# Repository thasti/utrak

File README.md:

# uTrak miniature tracker repository

## Abstract 
This repository contains software and hardware design files for uTrak - the tracker of a series of small high altitude balloons. The software is implemented for a MSP430 MCU, with test programs runnable on a PC.
project documentation can be found here: http://www.dooce.de/dokuwiki/doku.php?id=projekte:utrak:start

The following tasks shall be performed by the software:
* Filtering and reading GPGGA-sentences from GPS - extracting position, altitude
* Measuring supply voltage with internal ADC
* Reading die temperature with internal ADC
* Generating telemetry frames (Including position, altitude, supply voltage, temperature)
* Configuring the Si4060 transmitter IC
* Power management for MCU and external hardware
* Transmission of APRS position reports

## GPS input
The MSP430 USART is used to store one NMEA-sentence to RAM (from $ to newline). Filtering and processing is controlled by a simple finite state machine. Fix data (position and altitude) are extracted and converted to HAB telemetry compatible format and APRS frames.

## Telemetry generation
From valid GPS data and telemetry data, packets are generated. The text string is formatted to be sent in 7 bit ASCII over RTTY. APRS transmission is done on EU APRS frequency (144.800MHz) and the telemetry frequency.

## Power management
Focus of the software is to get power consumption down as low as possible. This includes using all the available power saving features of the MSP430 and peripherals:
* Low power modes of the MSP430
* Disabling unused peripherals
* Power down mode of the GPS module
* Disabling RF stage

# Hardware modifications
After v1, several modifications were made to the PCB to enable more features being possible. These include:

## TCXO as reference source
Frequency stability was totally unacceptable with crystals. In addition, the datasheet wrongly states that a TCXO has to be connected to XIN, while it has to be connected to XOUT.
Needed after commit: edc32003
- Instead of the XTAL, solder TCXO with clipped sine output, 16.3676Mhz.
- cut trace from C8 to XIN
- solder C=100pF instead as C8
- run wire from right pad of C8 to XOUT-pad (right pad of R5)
- solder bridge over R6
- do not place R4, R5 and R7

## TCXO source as clock input to MSP430
As DominoEX needs to me modulated coherently, MCU and PLL need to run off the same clock. Therefore, the Si4060 will buffer the TXCO signal and output it via GPIO to the MCU.
Needed after commit: ee2a82f8 until 752375ca
- solder wire from MSP430 QFN PAD 21 (PJ.4, XIN) to Si4060 QFN PAD 9 (GPIO0)

# Coarse Changelog
This changelog tries to summarize the development of the tracker firmware. See the git commit log for further information.

- 05-2014: Begin of development
- 09-2014: first test flight (RTTY 50 baud)
- 09-2014: change from the Linx-GPS to the uBlox M8Q module
- 10-2014: first flight with professional PCB & uBlox (0x01, 0x02)
- 11-2014: first flight with TCXO (0x03) - frequency stability improvement
- 10-2014: implementation of APRS transmission
- 11-2014: implementation of DominoEX16
- 11-2014: first flight with APRS & DominoEX16 (0x04)
- 12-2014: reverting to RTTY, now using 100 baud (0x05, 0x06)
- 07-2014: first good use of APRS: antenna now 2m dipole
- 07-2014: dropped support for DominoEX
- 07-2014: transmitting APRS only above a certain altitude (power savings)

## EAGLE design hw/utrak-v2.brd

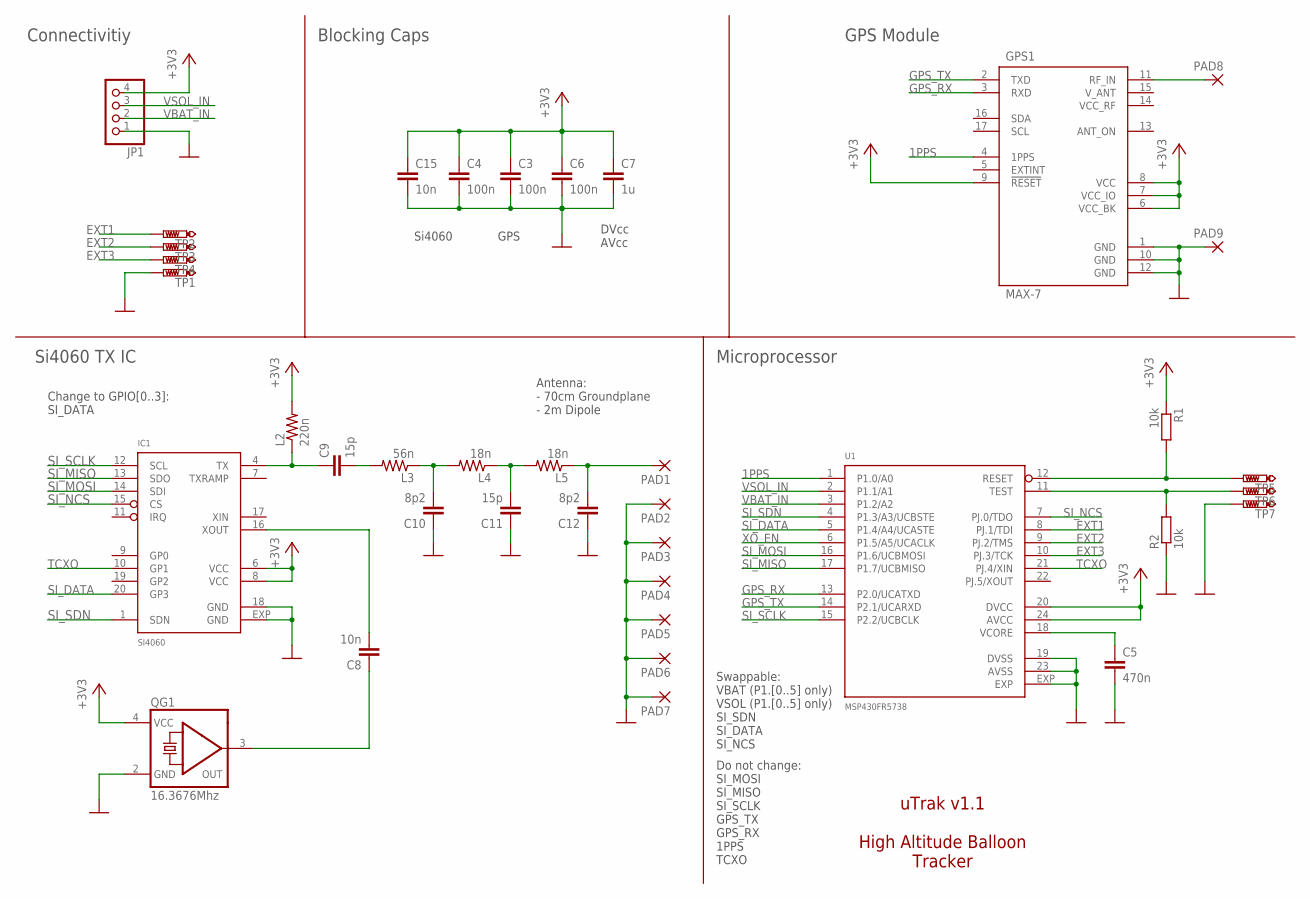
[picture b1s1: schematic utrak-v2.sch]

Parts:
C3, C4, C6: 100n; C0402; PARTNO 81-GRM155R71C104KA88
C5: 470n; C0603; PARTNO 81-GCM188R71C474KA5D
C7: 1u; C0603; PARTNO 81-GRM39R105K10
C8, C15: 10n; C0402; PARTNO 81-GRM155R71H103MA8D
C9, C11: 15p; C0402; PARTNO 81-GRM1555C1H150FA1D
C10, C12: 8p2; C0402; PARTNO 81-GRM1555C1H8R2BA1D
GPS1: MAX-7; UBLOX-7
IC1: SI4060; QFN20; PARTNO 634-SI4060-B1B-FMR
JP1: PINHD-1X4; 1X04
L2: 220n; R0603; PARTNO 994-0603CS-R22XGLW
L3: 56n; R0603; PARTNO 994-0603CS-56NXJLW
L4, L5: 18n; R0603; PARTNO 994-0603CS-18NXJLU
PAD1, PAD2, PAD3, PAD4, PAD5, PAD6, PAD7, PAD8, PAD9: SMD2; SMD1,27-2,54
QG1: 16.3676Mhz; CTS406
R1, R2: 10k; R0402; PARTNO 603-RC0402FR-0710KL
TP1, TP2, TP3, TP4, TP5, TP6, TP7: PTR1TP10SQ; TP10SQ
U1: MSP430FR5738; QFN24-4X4; PARTNO 595-SP430FR5738IRGER

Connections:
1PPS: GPS1.4 (1PPS), U1.1 (P1.0/A0)
+3V3: C3.1, C4.1, C6.1, C7.1, C15.1, GPS1.6 (VCC_BK), GPS1.7 (VCC_IO), GPS1.8 (VCC), GPS1.9 (!RESET), IC1.6 (VCC), IC1.8 (VCC), JP1.4, L2.2, QG1.4 (VCC), R1.1, U1.20 (DVCC), U1.24 (AVCC)
EXT1: TP2.TP, U1.8 (PJ.1/TDI)
EXT2: TP3.TP, U1.9 (PJ.2/TMS)
EXT3: TP4.TP, U1.10 (PJ.3/TCK)
GND: C3.2, C4.2, C5.2, C6.2, C7.2, C10.1, C11.1, C12.1, C15.2, GPS1.1 (GND), GPS1.10 (GND), GPS1.12 (GND), IC1.18 (GND), IC1.EXP (GND), JP1.1, PAD2.1, PAD3.1, PAD4.1, PAD5.1, PAD6.1, PAD7.1, PAD9.1, QG1.2 (GND), R2.1, TP1.TP, TP7.TP, U1.19 (DVSS), U1.23 (AVSS), U1.EXP
GPS_ANT_+: GPS1.11 (RF_IN), PAD8.1
GPS_RX: GPS1.3 (RXD), U1.13 (P2.0/UCATXD)
GPS_TX: GPS1.2 (TXD), U1.14 (P2.1/UCARXD)
unnamed: C8.2, IC1.16 (XOUT)
unnamed: C5.1, U1.18 (VCORE)
unnamed: C9.1, IC1.4 (TX), L2.1
unnamed: C9.2, L3.2
unnamed: C10.2, L3.1, L4.2
unnamed: C11.2, L4.1, L5.2
unnamed: C12.2, L5.1, PAD1.1
RST: R1.2, TP5.TP, U1.12 (RESET)
SI_DATA: IC1.20 (GP3), U1.5 (P1.4/A4/UCASTE)
SI_MISO: IC1.13 (SDO), U1.17 (P1.7/UCBMISO)
SI_MOSI: IC1.14 (SDI), U1.16 (P1.6/UCBMOSI)
SI_NCS: IC1.15 (CS), U1.7 (PJ.0/TDO)
SI_SCLK: IC1.12 (SCL), U1.15 (P2.2/UCBCLK)
SI_SDN: IC1.1 (SDN), U1.4 (P1.3/A3/UCBSTE)
TCXO: IC1.10 (GP1), U1.21 (PJ.4/XIN)
TCXO_OUT: C8.1, QG1.3 (OUT)
TST: R2.2, TP6.TP, U1.11 (TEST)
VBAT_IN: JP1.2, U1.3 (P1.2/A2)
VSOL_IN: JP1.3, U1.2 (P1.1/A1)
XO_EN: U1.6 (P1.5/A5/UCACLK)

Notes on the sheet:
GPS
GPS Module
Microprocessor
DVcc AVcc
Si4060
Blocking Caps
Do not change: SI_MOSI SI_MISO SI_SCLK GPS_TX GPS_RX 1PPS TCXO
Swappable: VBAT (P1.[0..5] only) VSOL (P1.[0..5] only) SI_SDN SI_DATA SI_NCS
Change to GPIO[0..3]: SI_DATA
Si4060 TX IC
Antenna: - 70cm Groundplane - 2m Dipole
Connectivitiy
uTrak v1.1 High Altitude Balloon Tracker

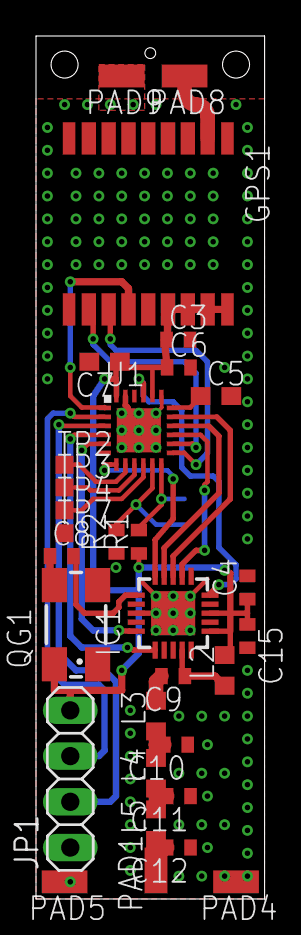
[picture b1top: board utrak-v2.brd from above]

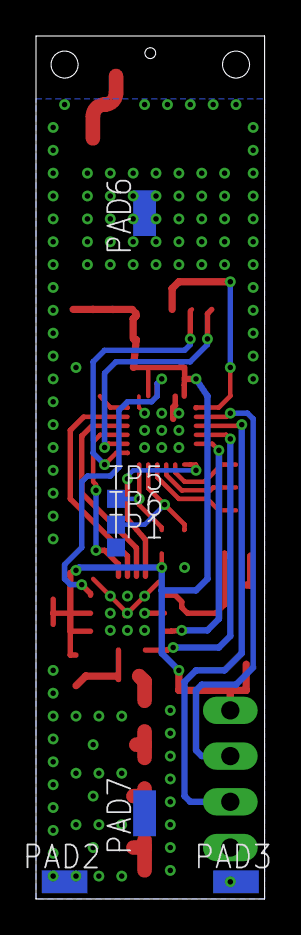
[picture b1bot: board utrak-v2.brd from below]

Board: 2 copper layers, 12.7 x 47.9 mm, 38 parts (7 on the bottom side), 28 nets.

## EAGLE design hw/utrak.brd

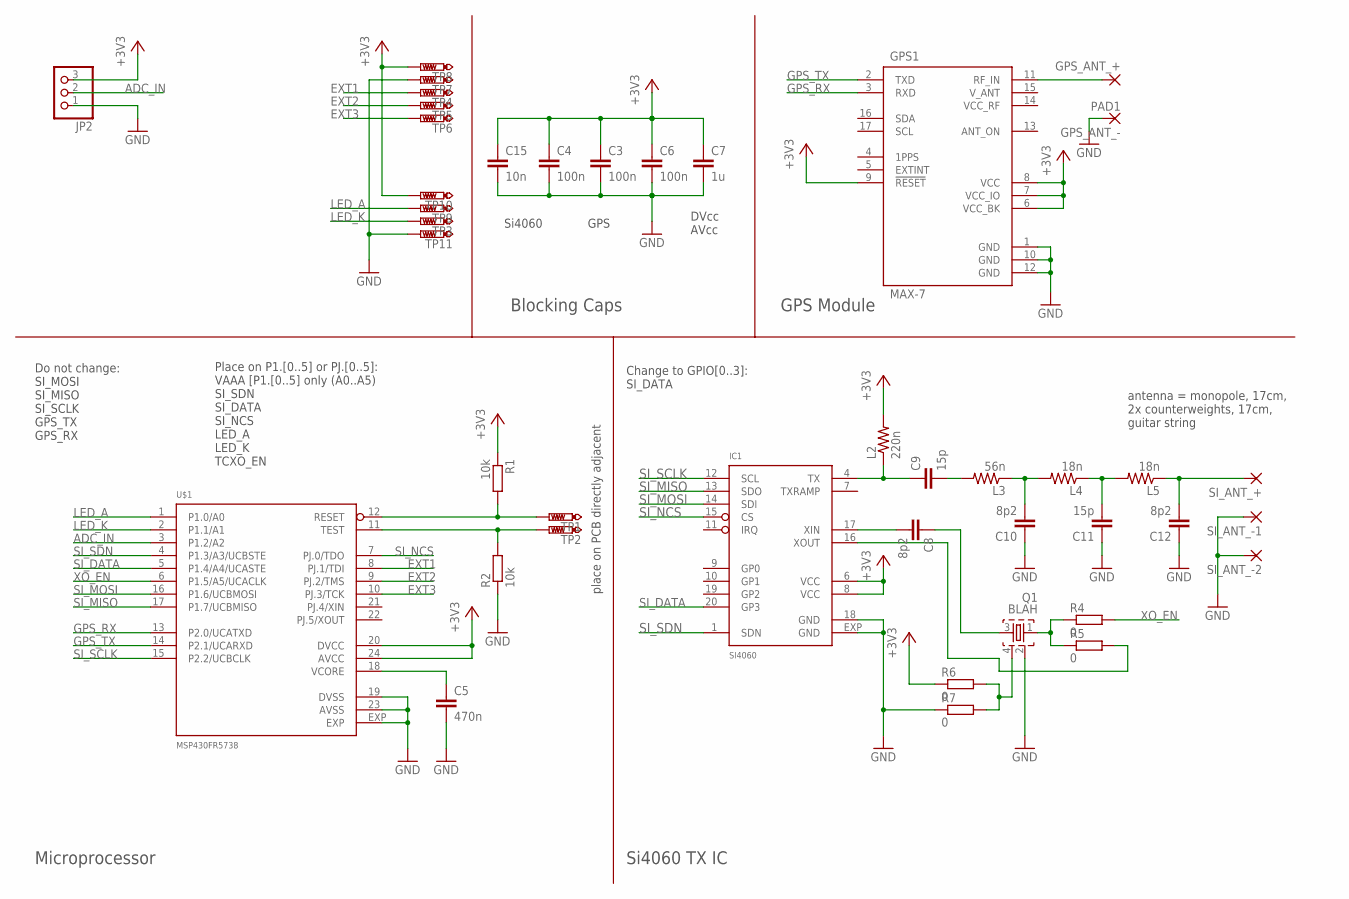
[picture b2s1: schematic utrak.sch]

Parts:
C3, C4, C6: 100n; C0603
C5: 470n; C0805
C7: 1u; C0603
C8: 8p2; C0402
C9: 15p; C0603
C10, C12: 8p2; C0603
C11: 15p; C0603K
C15: 10n; C0603
GPS1: MAX-7; UBLOX-7
GPS_ANT_+: SMD2; SMD1,27-2,54
GPS_ANT_-: PAD1; SMD1,27-2,0
IC1: SI4060; QFN20
JP2: PINHD-1X3; 1X03
L2: 220n; R0603
L3: 56n; R0603
L4, L5: 18n; R0603
Q1: BLAH; CTS406
R1, R2: 10k; R0402
R4, R5, R6, R7: 0; R0402
SI_ANT_+: SMD2; SMD1,27-2,54
SI_ANT_-1, SI_ANT_-2: SMD2; SMD1,27-2,54
TP1, TP2, TP3, TP4, TP5, TP6, TP7, TP8, TP9, TP10, TP11: PTR1TP07R; TP07R
U$1: MSP430FR5738; QFN24-4X4

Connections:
+3V3: C3.1, C4.1, C6.1, C7.1, C15.1, GPS1.6 (VCC_BK), GPS1.7 (VCC_IO), GPS1.8 (VCC), GPS1.9 (!RESET), IC1.6 (VCC), IC1.8 (VCC), JP2.3, L2.2, R1.1, R6.1, TP8.TP, TP10.TP, U$1.20 (DVCC), U$1.24 (AVCC)
ADC_IN: JP2.2, U$1.3 (P1.2/A2)
EXT1: TP4.TP, U$1.8 (PJ.1/TDI)
EXT2: TP5.TP, U$1.9 (PJ.2/TMS)
EXT3: TP6.TP, U$1.10 (PJ.3/TCK)
GND: C3.2, C4.2, C5.2, C6.2, C7.2, C10.1, C11.1, C12.1, C15.2, GPS1.1 (GND), GPS1.10 (GND), GPS1.12 (GND), GPS_ANT_-.P$1, IC1.18 (GND), IC1.EXP (GND), JP2.1, Q1.2, R2.1, R7.1, SI_ANT_-1.1, SI_ANT_-2.1, TP7.TP, TP11.TP, U$1.19 (DVSS), U$1.23 (AVSS), U$1.EXP
GPS_ANT_+: GPS1.11 (RF_IN), GPS_ANT_+.1
GPS_RX: GPS1.3 (RXD), U$1.13 (P2.0/UCATXD)
GPS_TX: GPS1.2 (TXD), U$1.14 (P2.1/UCARXD)
LED_A: TP9.TP, U$1.1 (P1.0/A0)
LED_K: TP3.TP, U$1.2 (P1.1/A1)
unnamed: C5.1, U$1.18 (VCORE)
unnamed: R2.2, TP2.TP, U$1.11 (TEST)
unnamed: R1.2, TP1.TP, U$1.12 (RESET)
unnamed: C9.1, IC1.4 (TX), L2.1
unnamed: C9.2, L3.2
unnamed: C10.2, L3.1, L4.2
unnamed: Q1.1, R4.1, R5.1
unnamed: C11.2, L4.1, L5.2
unnamed: C12.2, L5.1, SI_ANT_+.1
unnamed: Q1.4, R6.2, R7.2
unnamed: C8.1, Q1.3
unnamed: IC1.16 (XOUT), R5.2
unnamed: C8.2, IC1.17 (XIN)
SI_DATA: IC1.20 (GP3), U$1.5 (P1.4/A4/UCASTE)
SI_MISO: IC1.13 (SDO), U$1.17 (P1.7/UCBMISO)
SI_MOSI: IC1.14 (SDI), U$1.16 (P1.6/UCBMOSI)
SI_NCS: IC1.15 (CS), U$1.7 (PJ.0/TDO)
SI_SCLK: IC1.12 (SCL), U$1.15 (P2.2/UCBCLK)
SI_SDN: IC1.1 (SDN), U$1.4 (P1.3/A3/UCBSTE)
XO_EN: R4.2, U$1.6 (P1.5/A5/UCACLK)

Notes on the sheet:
GPS
GPS Module
Microprocessor
DVcc AVcc
Si4060
Blocking Caps
Do not change: SI_MOSI SI_MISO SI_SCLK GPS_TX GPS_RX
Place on P1.[0..5] or PJ.[0..5]: VAAA [P1.[0..5] only (A0..A5) SI_SDN SI_DATA SI_NCS LED_A LED_K TCXO_EN
Change to GPIO[0..3]: SI_DATA
Si4060 TX IC
antenna = monopole, 17cm, 2x counterweights, 17cm, guitar string
place on PCB directly adjacent

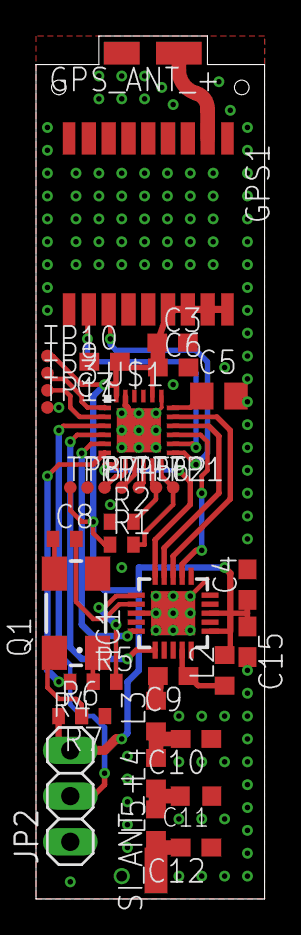
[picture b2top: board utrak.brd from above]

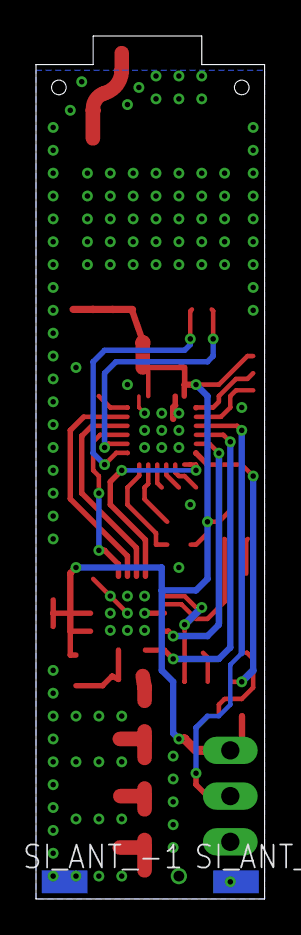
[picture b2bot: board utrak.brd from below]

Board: 2 copper layers, 12.7 x 47.9 mm, 42 parts (2 on the bottom side), 31 nets.

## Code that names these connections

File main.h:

/*
 * main tracker software
 *
 * Stefan Biereigel
 *
 */

#ifndef MAIN_H_
#define MAIN_H_

/* payload name */
#define PAYLOAD_NAME "DO9EHP/AM"
/* payload telemetry interval
 * can be set for APRS only and for RTTY + APRS
 */
#define TLM_APRS_INTERVAL	120
#define TLM_RTTY_INTERVAL	120
/* time offset for APRS backlog transmissions */
#define TLM_BACKLOG_OFFSET	15
/* how often a fix should be requested when transmitting blips (after power up) */
#define BLIP_FIX_INTERVAL	1

/* whether RTTY telemetry shall be transmitted at all */
#define TLM_RTTY
//#define TLM_RTTY_ONLY
//#define SOLAR_POWER

/* telemetry string prefix for RX syncronisation */
#define SYNC_PREFIX		"   $$"
/* telemetry string postfix for tlm parser */
#define TX_BUF_POSTFIX		"\n\n"

/* number of idle bits to transmit before beginning tlm string tx */
#define NUM_IDLE_BITS	32

/* length of non-GPS-telemetry fields */
#define LAT_LENGTH		9
#define LON_LENGTH		10
#define TIME_LENGTH		6
#define SAT_LENGTH		2
#define ALT_LENGTH_MAX		5
#define VOLT_LENGTH		4
#define VSOL_LENGTH		4
#define TEMP_LENGTH		2
#define CHECKSUM_LENGTH		4
/* sentence id is variable length */
#define SENT_ID_LENGTH_MAX	5

#define TX_BUF_POSTFIX_LENGTH	sizeof(TX_BUF_POSTFIX) - 1
/* offset from buffer start to telemetry data */
#define TX_BUF_START_OFFSET 	sizeof(SYNC_PREFIX "$$" PAYLOAD_NAME ",") - 1
#define TX_BUF_SENT_ID_START	TX_BUF_START_OFFSET
#define TX_BUF_TIME_START	TX_BUF_SENT_ID_START + tlm_sent_id_length + 1
#define TX_BUF_LAT_START	TX_BUF_TIME_START + TIME_LENGTH + 1
/* lat and lon fields are one char longer for +/- */
#define TX_BUF_LON_START	TX_BUF_LAT_START + LAT_LENGTH + 1 + 1
#define TX_BUF_ALT_START	TX_BUF_LON_START + LON_LENGTH + 1 + 1
#define TX_BUF_SAT_START	TX_BUF_ALT_START + tlm_alt_length + 1
#define TX_BUF_VOLT_START	TX_BUF_SAT_START + SAT_LENGTH + 1
#define TX_BUF_VSOL_START	TX_BUF_VOLT_START + VOLT_LENGTH + 1
/* temperature field is one char longer for +/- */
#define TX_BUF_TEMP_START	TX_BUF_VSOL_START + VSOL_LENGTH + 1
#define TX_BUF_CHECKSUM_START	TX_BUF_TEMP_START + TEMP_LENGTH + 1 + 1
#define TX_BUF_POSTFIX_START	TX_BUF_CHECKSUM_START + CHECKSUM_LENGTH
#define TX_BUF_FRAME_END	TX_BUF_POSTFIX_START + sizeof(TX_BUF_POSTFIX) - 1;
/* checksum parameters */
#define TX_BUF_CHECKSUM_BEGIN	sizeof(SYNC_PREFIX "$$") - 1
#define TX_BUF_CHECKSUM_END	TX_BUF_CHECKSUM_START - 1

#define TX_BUF_MAX_LENGTH	sizeof(SYNC_PREFIX "$$" PAYLOAD_NAME) - 1 + 1 + \
				SENT_ID_LENGTH_MAX + 1 + TIME_LENGTH + 1 + LAT_LENGTH + 1 + LON_LENGTH + 1 + \
				ALT_LENGTH_MAX + 1 + SAT_LENGTH + 1 + VOLT_LENGTH + 1 + VSOL_LENGTH + 1 + TEMP_LENGTH + \
				sizeof("*") - 1 + CHECKSUM_LENGTH + TX_BUF_POSTFIX_LENGTH

/* buffer sizes */
#define NMEA_BUF_SIZE	83

/* Port 1 */
#define LED_A	BIT0
#define VSOL_IN	BIT1
#define VBAT_IN	BIT2
#define SI_SHDN	BIT3
#define SI_DATA	BIT4
#define MOSI	BIT6
#define MISO	BIT7

/* Port 2 */
#define RXD	BIT1
#define TXD	BIT0
#define SCLK	BIT2

/* Port J */
#define CS	BIT0

/* Timer compare defitions */
/* as some values need fine tuning to keep error in a margin and are constrained, */
/* these should be recalculated manually when the CPU frequency is changed  */
/* NCO is running at 26400 hz (lowest common denominator of 1200*2 and 2200*2) */
#define N_APRS_NCO	303		/* DCO_freq / 26400 */

#define N_TLM	40000 - 1		/* DCO_freq / TLM rate / 2 */
#define TLM_HZ	100			/* tlm rate in Hz */

/* ADC calibration locations */
#define CALADC10_15V_30C  *((unsigned int *)0x1A1A)   // Temperature Sensor Calibration-30 C
#define CALADC10_15V_85C  *((unsigned int *)0x1A1C)   // Temperature Sensor Calibration-85 C

#endif

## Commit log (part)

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2014-05-12 empty README
2014-05-12 initial README
2014-05-13 add atoi32 and simple unit test
2014-05-14 add more string helper routines
2014-05-14 add NMEA data extraction
    this software state can validate if a received sentence is a
    GPGGA-sentence and if it contains valid fix data. if so, data is
    extracted and written to char arrays of fixed lengths. these can be
    placed inside the APRS string and therefore modify the sent string -
    therefore keeping down memory consumption
    pc unit tests are included
2014-05-18 update design changes in README
2014-05-18 add CRC routines for checksum generation
2014-05-18 add si4060 library
    this includes all neccesary defines for using the Si4060 for TX only,
    using either RAW GPIO TX mode or modulating via changing the frequency
    register via SPI.
2014-05-18 add needed commands/properties/value definitions
2014-05-19 update si4060 register/property map
2014-05-19 add setup routine
2014-05-19 initalise GPIO0 as input
2014-05-19 add license file
2014-05-19 rename tx directory
2014-05-19 remove TODO for synth values - defaults are OK
2014-05-19 add flexible frequency calculation
2014-05-19 change CTS-polling and implement change-state-cmd
    CTS shall be polled to be 0xFF, and not just "different from 0x00",
    therefore we do that now. to end transmissions, the change-state command
    was implemented, as i don't know of any other way to stop transmission
    in the direct TX mode...
2014-05-20 adopt nmea output string format
2014-05-20 add (simple) makefile for gps parser
2014-05-20 add i16tox, fix some style errors
2014-05-21 add test and implementation for CRC16
2014-05-22 add simple Makefile for utilities
2014-05-28 make SPI debug format bus-pirate compatible
2014-05-29 add main infrastructure - uart loopback 9k6
2014-05-29 move files to top level directory
2014-05-29 move util folder to top level
2014-05-29 make test modules for gps,si4060,util
2014-06-01 SPI fixes, si4060 init
    spi write command now also returns the RXed byte. SPI init is done in
    code now, but seems not to be working (tbc). main()-testcode monitors
    the configured GPIOs, which seem not to get initialised.
    further investigation is needed here!
2014-06-04 move si4060 power up before setup
2014-06-04 add SPI hardware functions
2014-06-04 remove hardware access from si4060.c, fix typos
    this commit cleans up some debugging outputs from the si4060 and fixes a
    define bug, which misspelled TCXO
2014-08-02 whitespace fixes, si4060 now working
2014-08-02 add API documentation, move si4060 routines to library
2014-08-03 coding style fixes, GPS initialisation, whitespace
    this commit fixes all remaining whitespace issues and makes function
    naming not using CamelCase but underscore_spaces.
    the rationale will be, that variables have CamelCase spelling and
    function names should be underscore_seperated.
    also: GPS UART communication was tested and works well. the GPS can be
    set to output GPGGA-sentences only, and AlwaysLocate mode can be entered
2014-08-04 add GPS helpers, main structure, more commenting
2014-08-04 test blips, add time from GPGGA
2014-08-04 implement RTTY transmission logic, working
2014-08-04 add test case to CRC test, for MSP430 compat
2014-08-04 implement CRC on MSP430 HW, construct tlm frame
    this implements the CRC generation for the payload on the msp430 crc
    hardware. this spares the cost of the software implementation.
    also, the telemetry frame should now be correctly filled with
    information
2014-08-05 longer lat/lon, fix buffer lengths
2014-08-05 enable watchdog, temp format fix, adc enabled
    watchdog: as it was observed that the Si4060 locks up occasionally
    (after power up, as known..) caused by clock issues, and in case the
    software contains error for flight - the watchdog was enabled with about
    11 seconds reset interval. this is more than enough for all working
    situations. tested and verified ok!
    temp format fix: the temperature is now output as signed and correctly
2014-08-05 doc fixes, error indication
2014-08-06 add possible sync chars before tlm string begin
2014-08-08 change altitude unit to meters
2014-08-08 add variable length field feature
    this commit first adds a helper routine: i16toav - this converts a 16
    bit number to a variable-length string. when called, it returns how
    many characters were needed.
    this routine is used for the sentence_id field, which is made variable
    length. it only consumes as much characters as it needs, minimum 1,
    maximum 5.
2014-08-09 convert altitude field to var length
2014-08-09 make sentence counter 16 bit
2014-08-13 adapt pins to production hardware
2014-08-15 add LED anode/cathode to code, blink while blip-tx
2014-08-18 add hardware design files
2014-09-01 add new hardware files
2014-09-26 integrate u-Blox GNSS module
    with the change from the Linx GPS to the u-Blox modules, some software
    changes were neccesary. it requires much more configuration, therefore
    the GPS init routines were factored out into gps.c
    as it also utilizes different talker IDs, GPGGA was removed and changed
    to a generic *GGA
    at last, the new powersaving methods were implemented, but are yet to be
2014-09-27 move test software to test/ directory
2014-09-28 enable saving of GPS configuration
2014-09-29 GPS locked transmitter frequency
    this commit enables the time pulse feature in the uBlox GPS module. a
    small hardware modification enables the tracker to be used with the time
    pulse as the clock input.
2014-09-30 diffrent blip speeds (fix / no fix)
2014-09-30 compat. NMEA always has 2 chars for sats
2014-09-30 add timeout to si4060 reads
2014-09-30 revert changes to use the uBlox TP as clk source
    it soon got clear that the timepulse from the uBlox is not suitable as a
    reference clock to the Si4060.
    it often locks up, hanging the software, etc. a timeout feature for
    failed start attempts was added, but is outcommented now, as it only
    hides problems. if this should be handled for real, a proper
    reset/reinit framework would be needed.
2014-10-12 describe functionality and hardware modifications
2014-10-12 add frequency counter feature
    remove debugging feature
    change names of gpios with new usage
    activate time pulse feature in the uBlox GPS module with 1 pulse per second
    add frequency counter ISRs
    frequency readout only possible with debugging interface
2014-10-12 activate clock output on GP2 of Si4060
2014-10-12 add TODO file
2014-10-19 si4060: use SPI instead of data pin for RTTY and pips
2014-10-19 Revert "si4060: use SPI instead of data pin for RTTY and pips"
    This reverts commit 48879f4e3160e3ea8a3c2ad2d9387ca7d8d9ede0.
2014-10-21 SPI CS delay, Si4060 change_state exposed
2014-10-21 faster SPI and core CPU speed
    CPU and SPI now use the DCO frequency (5,37MHz)
2014-10-21 add utility to generate sine tables
2014-10-21 new tick infrastructure
2014-10-21 sin_table: write header file
2014-10-22 solidify faster communication with Si4060
2014-10-22 transmit sine wave in FM FSK
    this commit makes the Si4060 transmit a 1200 Hz sine wave, frequency
    modulated with +-3kHz deviation. works well so far, as soon as the
    si4060 started to power up in the first place. afterwards, SPI
    communication is rock solid, no hangs or crashes observed. the Si4060
    seems to take longer to update the offset-register every second or so,
    maybe because of internal interrupts?
2014-10-22 add debug uart output for frequency counter
2014-10-23 increased DCO to 8MHz
2014-10-23 correct reset behaviour for Si4060
2014-10-23 optimisations
    the sin_table was not a const[], consuming much RAM and leaving too
    little stack for the program.
    inlined one-time-use-functions
    removed static variables where unneccesary
2014-10-23 util: make sin_table a const
2014-10-23 major refactoring, si4060 reset more margin
    main.c was cluttering up with telemetry, aprs, etc. therefore all
    functions inside it that belong to a special part of the software have
    been refactored inside external files.
    aprs.c contains everything related to FM FSK.
    hw.c contains hardware initialisation
    tlm.c contains everything related to normal RTTY telemetry
2014-10-23 introduce dco frequency measurement
2014-10-23 don't lock to gps
2014-10-23 implement APRS logic
2014-10-24 fix some bugs in APRS
2014-10-24 APRS transmission working
2014-10-25 correct WIDE path
2014-10-25 some adaptions for 8MHz DCO
2014-10-25 revert false fixes, correct baud rate
    This reverts commit 28098a618c0abd4fee455dffc3710b142dfca8bd.
    also, automatic APRS transmission is disabled
    baud rate fix (correct values for 8MHz DCO)
2014-10-25 finish APRS implementation, schedule
    APRS is now sent on a regular basis, namely before every TLM string - on
    70cm only for now. the FM middle frequency is used as the middle for the
    RTTY transmission.
2014-10-26 remove dead code, overflow counters static
2014-10-28 transmit APRS on 2m and 70cm
    the software now switches between 2m and 70cm frequencies for
    transmission of APRS packets.
    some infrastructure was added, maybe the second sine table can be
    optimized by runtime-calculation of sin_2m * 0,3125 in the future. for
    now we have enough FRAM left.
2014-10-28 bump payload name, APRS TX delay, copy-paste-error
2014-10-28 disable uart while measurement
2014-10-30 disable APRS since it's not working with the new TCXO
2014-11-06 new parameters for APRS NCO
2014-11-07 separate RTTY from general telemetry code
    as the next addition will be DominoEX, RTTY code is factored out into
    its own file.
2014-11-10 add dominoEX varicode table
2014-11-10 implementation working
    telemetry is now generated and transmitted in DominoEX16 format.
2014-11-10 bump payload name
2014-11-10 bump APRS SSID
2014-11-30 new timer infrastructure
    the usage of timers was reworked. Before this, every clock was derived
    from a fast tick (the APRS NCO sample rate), which was sufficient until
    now.
    Three major things caused the rework: New clock source (16.367600MHz
    TCXO), aprs baud rate not being able to have small enough error, exact
    tuning requirement for DominoEX baud rate.
2015-03-05 fix frequency for 0x05
2015-03-12 increase tlm period, bump callsign
2015-07-06 0x07 flight adaptations
2015-07-10 transmit RTTY telemetry only below altitude of 4km
    for power saving reasons, and because APRS worked out so well for 0x07,
    continous RTTY transmissions seem no longer needed. they are really
    helpful for recovery anyway, so they are re-enabled below 4km of
    altitude.
2015-07-10 remove support for DominoEX
2015-07-10 remove support for 70cm APRS
2015-07-10 add a coarse changelog to the README
2015-07-20 bump to 0x08, transmit temperature and voltage in APRS comment
2015-07-24 disable APRS NCO timer when not transmitting APRS
    this fixes the bug introduced by the new APRS infrastructure, causing
    random resets before the RTTY transmission - likely a race condition
    between serial input, the telemetry timer and the APRS NCO timer
    interrupt routine.
2015-07-24 use ARPS compressed comment telemetry
2015-07-27 cleanup globals before NMEA extraction
2015-07-29 split buffer preparation and transmission initialisation
2015-07-29 remove last occurrences of dominoEX
2015-07-29 implement APRS timestamp (DHM)
2015-07-29 add missing GPS fix file
2015-07-30 implement backlog transmissions
2015-07-31 remove unnecessary extern declarations
2015-07-31 remove unnecessary tools/utilities
2015-07-31 bump callsign to 0x0b
2015-08-06 revert to 0x0a, more backlog, greater interval, aprs only
2015-09-25 changes for 0x0b
2016-04-19 bump callsign to 0x0c
2016-04-22 use ON/OFF-mode for GPS instead of cyclic tracking
2021-01-24 0x12 updates
